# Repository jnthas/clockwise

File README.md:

**[Latest version 1.4.4 released!](https://github.com/jnthas/clockwise/releases/tag/v1.4.4)** | [See full change log](https://github.com/jnthas/clockwise/blob/main/CHANGELOG.md#144---2026-10-05)

---

**Clockwise** is an open-source smart wall clock that you can easily build yourself.  
It only needs:

- 64x64 RGB LED Matrix (HUB75 or HUB75E)
- ESP32 dev board
- 5V 3A power supply
- Jumpers

To simplify assembly, you can also use the [**WiseShield-32 DIY PCB kit**](https://www.elecrow.com/clockwise-diy-kit.html) — created in partnership with Elecrow especially for Clockwise.

---

## Features

- Real-time clock with customizable themes ("Clockfaces")
- Web-based interface for configuration
- [MCP tools and a desktop-client bridge](docs/MCP.md) for local AI-assisted control
- Open-source hardware and firmware
- Compatible with various PCBs or just simple wiring
- Community-driven

---

## Quick Start

### 1. Required Hardware

If you want to build it from scratch, you will need at least these components below. Follow the instructions on [Wiki]() to assemble it. 
- 64x64 RGB LED matrix (HUB75 or HUB75E)
- ESP32 Dev Board
- 5V 3A power supply
- Jumpers

Alternatively, we created a custom PCB that simplifies this process a lot. The kit includes not only the PCB but all components including sensors to make your clock smarter. Check the [WiseShield-32 PCB kit](https://www.elecrow.com/clockwise-diy-kit.html) out now!

### 2. Flash Firmware

- Go to: [https://clockwise.page](https://clockwise.page)
- Follow the on-screen steps to flash Clockwise and configure WiFi

For detailed instructions:  
👉 [See Wiki: Getting Started](https://github.com/jnthas/clockwise/wiki/%F0%9F%9A%80-Getting-Started)

---

## Clockfaces Gallery

You can choose from many creative Clockfaces — or make your own:

Mario Bros | Words | World Map | Castlevania | Pacman | Pokedex | Canvas
:--:|:--:|:--:|:--:|:--:|:--:|:--:
 |  |  |  |  |  | 

> Canvas is a special type of Clockface that is capable of rendering different themes described in a JSON file. More about **Canvas Clockface**: [Wiki page](https://github.com/jnthas/clockwise/wiki/Canvas-Clockface)

---

## How to Build

You can start developing and customizing Clockwise in two different ways:

1. **PlatformIO** — advanced usage for developers  
2. **ESP-IDF** — for full control  

👉 [Both are described in the Flashing section of the Wiki](https://github.com/jnthas/clockwise/wiki/%F0%9F%92%BE-Flashing-the-Firmware)

---

## Advanced Configuration

Clockwise offers a flexible set of options that you can adjust through its built-in Settings page:

* **WiFi settings** — easily update your network details without reflashing
* **Timezone & NTP server** — sync the clock accurately with automated NVS POSIX caching
* **Display brightness** — manual or smoothed automatic control (with optional LDR sensor)
* **Display rotation** — adjust orientation (0°, 90°, 180°, 270°) to match your setup
* **Clockface selection** — switch between installed Clockfaces or use Canvas themes
* **RGB order correction** — swap Blue/Green or Blue/Red pins to fix color mismatches
* **Hardware settings** — configure matrix shift driver (FM6124, etc.), I2S clock speed, and E-line pin
* **POSIX timezone string** — fine-tune timezone behavior or use offline overrides

👉 See the full guide here: [Advanced Configuration Wiki](https://github.com/jnthas/clockwise/wiki/%E2%9A%99%EF%B8%8F-Configuring-Clockwise)

---

## Community & Contributions

- Join the [Clock Club](https://github.com/jnthas/clock-club) to create your own Clockfaces
- Contributions and pull requests are welcome!  
👉 [Contributing Guide](https://github.com/jnthas/clockwise/wiki/%F0%9F%A4%9D-Contributing)

---

## License

Clockwise is released under the MIT License.

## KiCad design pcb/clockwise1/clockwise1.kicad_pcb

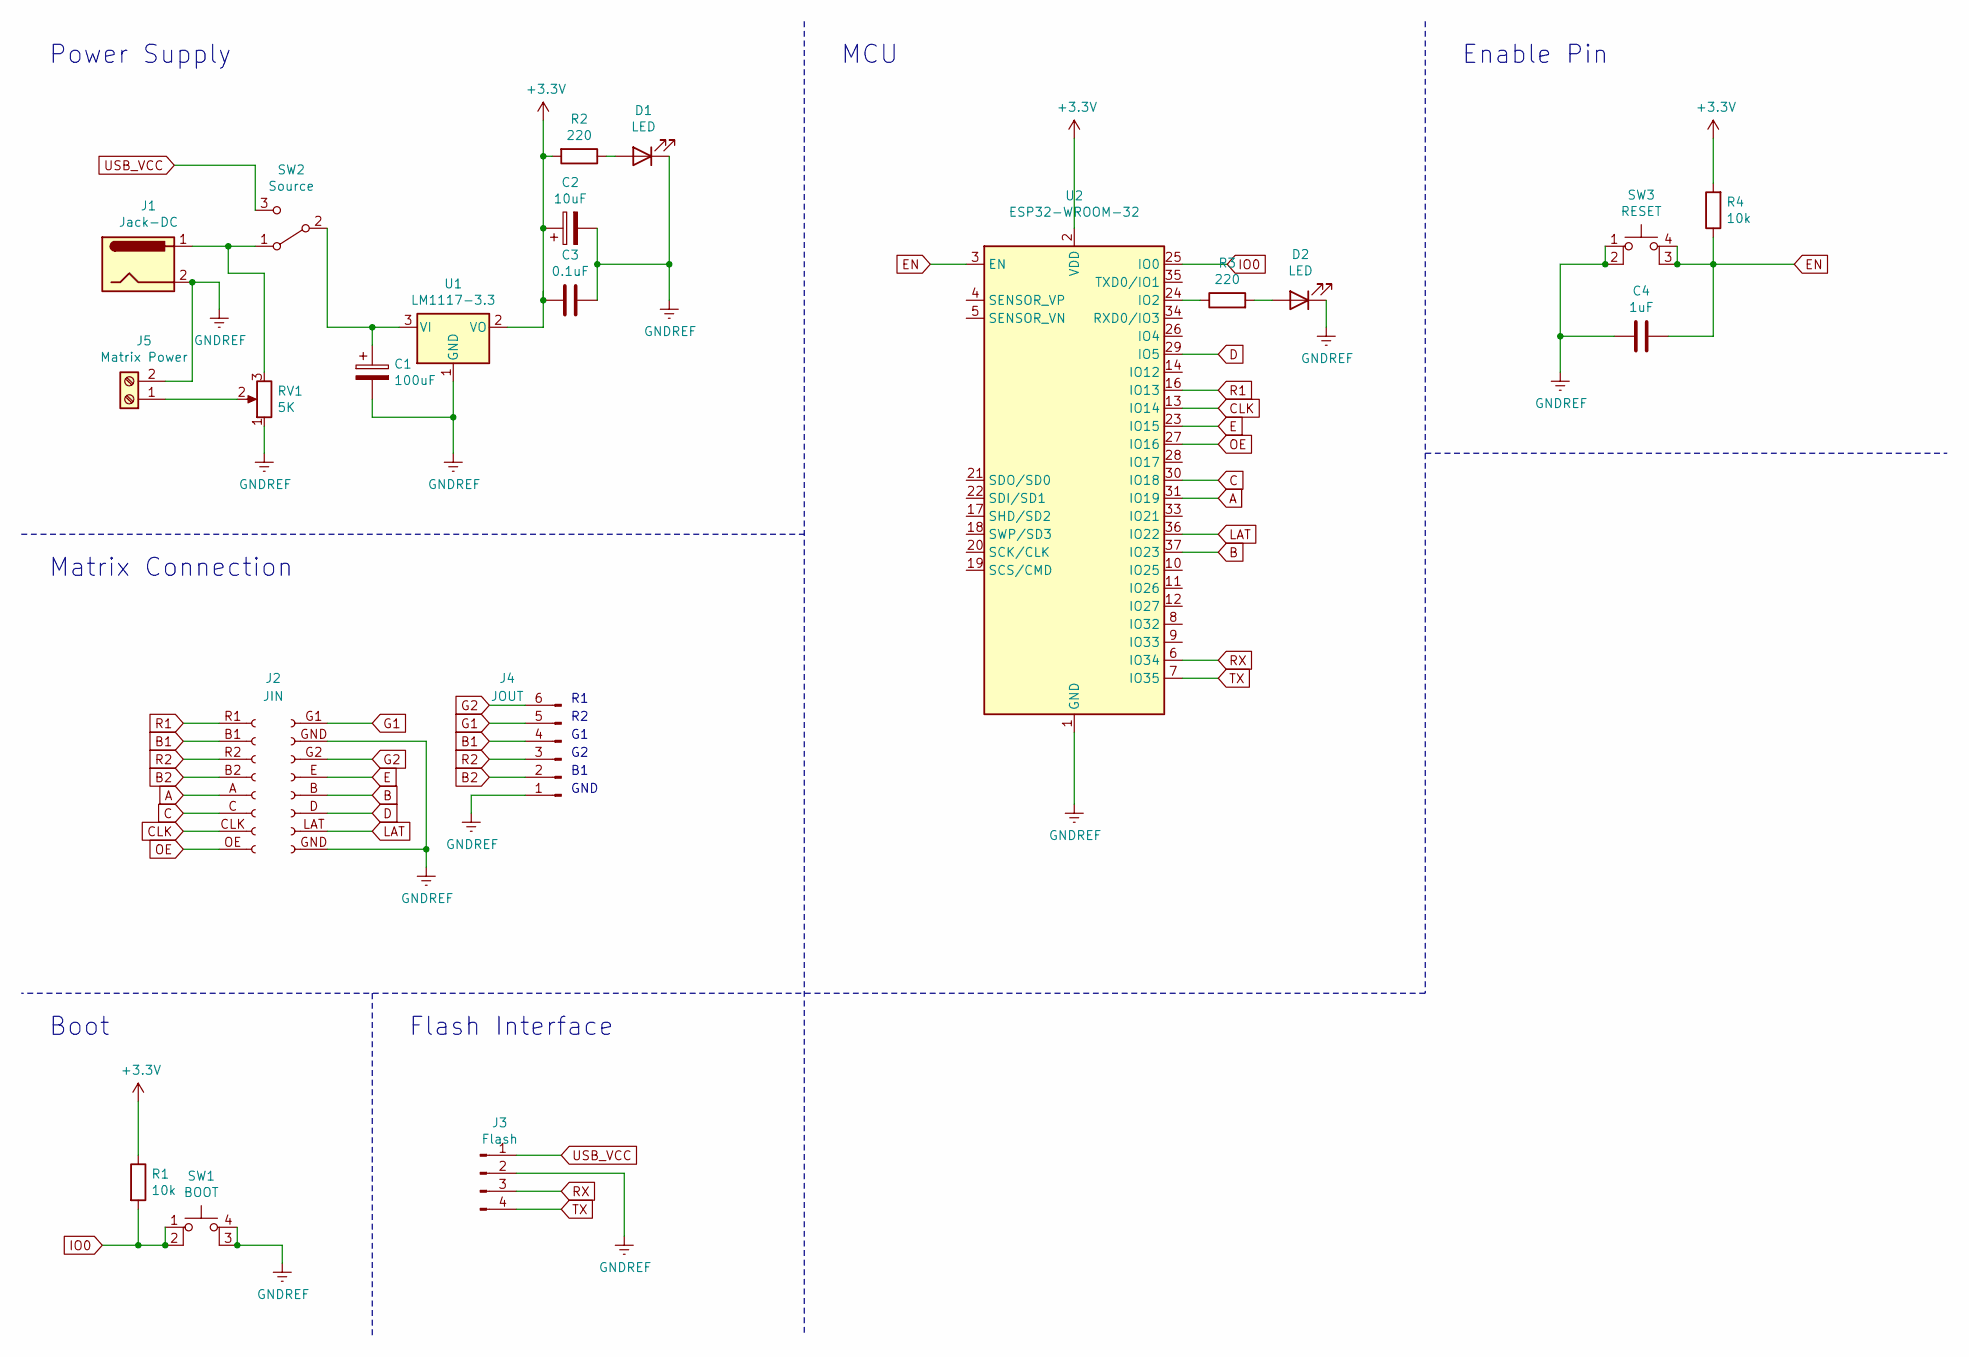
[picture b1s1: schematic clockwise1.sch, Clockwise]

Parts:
C1: 100uF; CP_Radial_D10.0mm_P5.00mm
C2: 10uF; CP_Radial_D10.0mm_P3.50mm
C3: 0.1uF; C_Disc_D5.0mm_W2.5mm_P5.00mm
C4: 1uF; CP_Radial_D10.0mm_P3.50mm
D1, D2: LED; LED_D3.0mm
J1: Jack-DC; BarrelJack_Horizontal
J2: JIN; PinSocket_2x08_P2.54mm_Vertical_SMD_LedMatrix
J3: Flash; PinHeader_1x04_P2.54mm_Vertical
J4: JOUT; PinHeader_1x06_P2.54mm_Vertical
J5: Matrix Power; TerminalBlock_Phoenix_MKDS-1,5-2-5.08_1x02_P5.08mm_Horizont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
R1, R4: 10k; R_Axial_DIN0207_L6.3mm_D2.5mm_P10.16mm_Horizontal
R2: 220; R_Axial_DIN0207_L6.3mm_D2.5mm_P10.16mm_Horizontal
R3: 220; R_Axial_DIN0207_L6.3mm_D2.5mm_P15.24mm_Horizontal
RV1: 5K; Potentiometer_Bourns_3386F_Vertical
SW1: BOOT; SW_PUSH
SW2: Source; SW_Slide_1P2T_CK_OS102011MS2Q
SW3: RESET; SW_PUSH
U1: LM1117-3.3; SOT-223
U2: ESP32-WROOM-32

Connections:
+3V3: C2.1, C3.2, R1.1, R2.2, R4.2, U1.2 (VO), U2.2 (VDD)
A: J2.A (Pin_5), U2.31 (IO19)
B: J2.B (Pin_12), U2.37 (IO23)
B1: J2.B1 (Pin_2), J4.4
B2: J2.B2 (Pin_4), J4.2
C: J2.C (Pin_6), U2.30 (IO18)
CLK: J2.CLK (Pin_7), U2.13 (IO14)
D: J2.D (Pin_11), U2.29 (IO5)
E: J2.E (Pin_13), U2.23 (IO15)
EN: C4.1, R4.1, SW3.3 (K), SW3.4 (A), U2.3 (EN)
G1: J2.G1 (Pin_16), J4.5
G2: J2.G2 (Pin_14), J4.6
GNDREF: C1.2, C2.2, C3.1, C4.2, D1.1 (K), D2.1 (K), J1.2, J2.GND (Pin_15), J3.2, J4.1, J5.2, RV1.1, SW1.3 (K), SW1.4 (A), SW3.1, SW3.2, U1.1 (GND), U2.1 (GND), U2.15 (GND), U2.38 (GND), U2.39 (GND)
IO0: R1.2, SW1.1, SW1.2, U2.25 (IO0)
LAT: J2.LAT (Pin_10), U2.36 (IO22)
unnamed: C1.1, SW2.2 (B), U1.3 (VI)
unnamed: D1.2 (A), R2.1
unnamed: D2.2 (A), R3.2
unnamed: J1.1, RV1.3, SW2.1 (A)
unnamed: J5.1, RV1.2
unnamed: R3.1, U2.24 (IO2)
OE: J2.OE (Pin_8), U2.27 (IO16)
R1: J2.R1 (Pin_1), U2.16 (IO13)
R2: J2.R2 (Pin_3), J4.3
RX: J3.3, U2.6 (IO34)
TX: J3.4, U2.7 (IO35)
USB_VCC: J3.1, SW2.3 (C)

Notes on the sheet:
Enable Pin
Power Supply
Boot
Flash Interface
Matrix Connection
MCU
GND

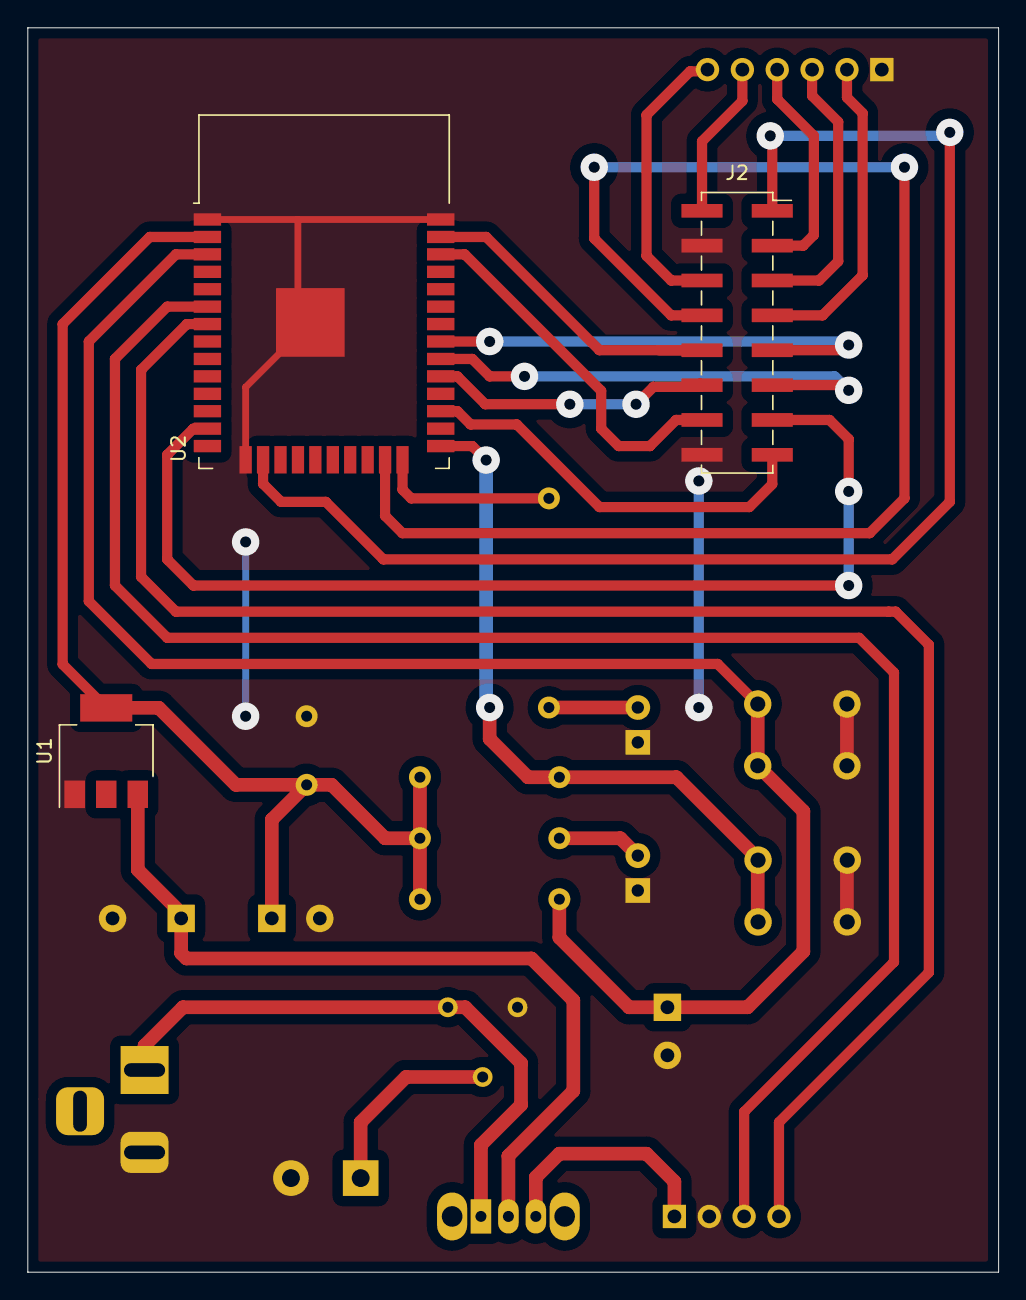
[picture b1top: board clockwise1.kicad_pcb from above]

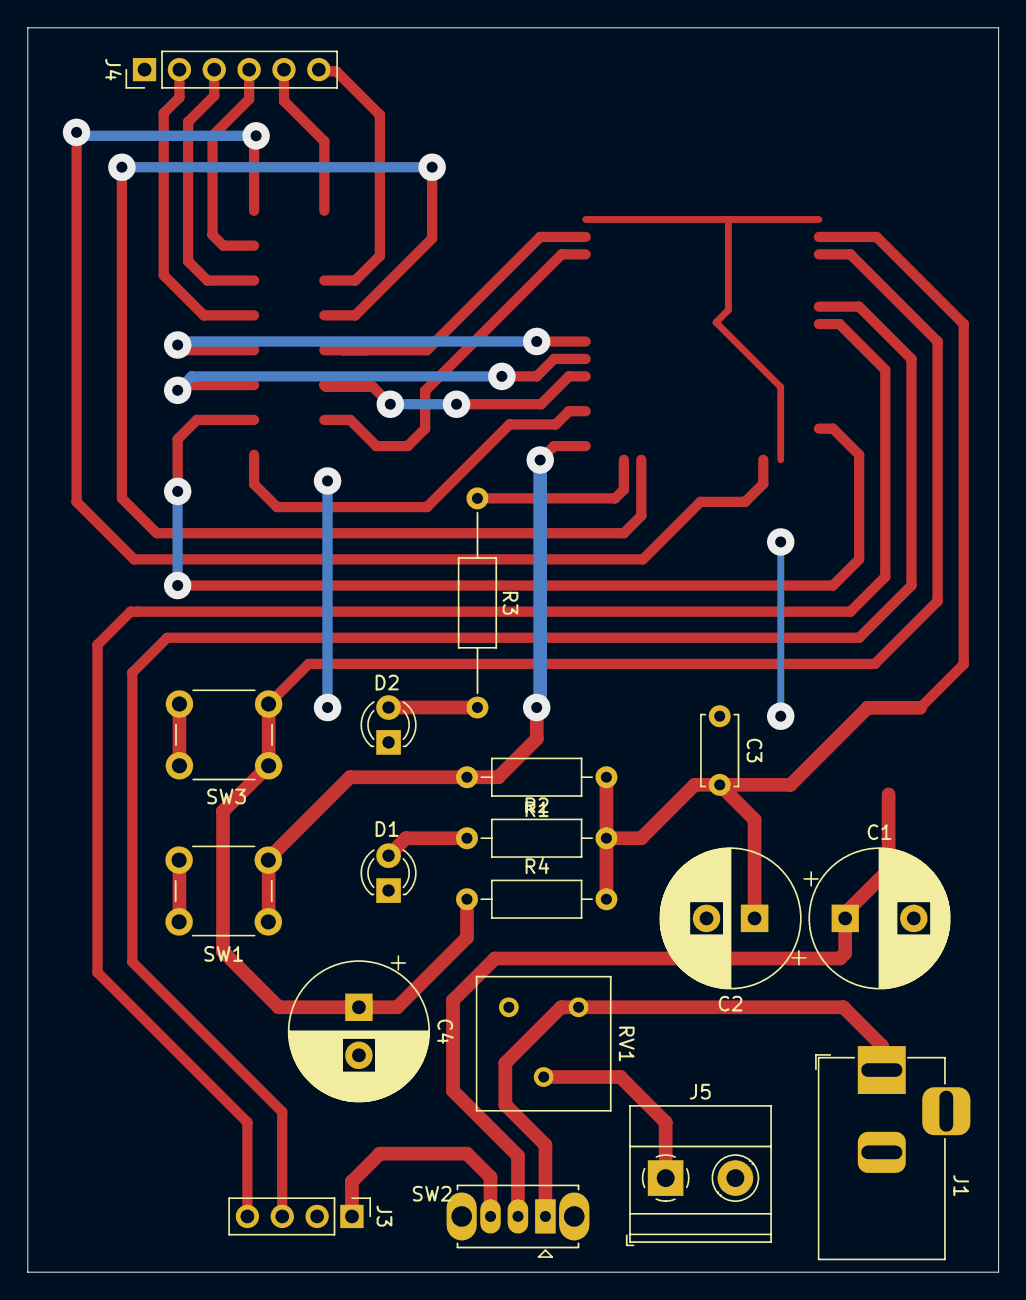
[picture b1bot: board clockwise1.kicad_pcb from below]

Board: 2 copper layers, 70.7 x 90.7 mm, 21 parts (18 on the bottom side), 27 nets.

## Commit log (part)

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2022-07-09 update clockfaces
2022-07-18 ci pipeline
2022-07-18 clockwise ci
2022-07-22 new version published
2022-07-22 new version published - cw-cf-0x03
2022-07-22 new version published - cw-cf-0x02
2022-07-22 new version published - cw-cf-0x04
2022-07-22 new version published - cw-cf-0x01
2022-07-22 reafactoring folder structure
2022-07-22 remove symlink
2022-08-07 add pacman clockface
2022-08-07 Add pacman build
2022-08-07 new version published - cw-cf-0x05
2022-08-07 new commits
2022-08-07 update cw-cf-05
2022-08-07 update submodules
2022-08-09 Add configuring wifi instructions
2022-09-26 Fix warning in WiFiConnect.H
    When compiling the code with '-Werror=format' the code fails to compile with this error:
    ```
    WiFiConnect.h: In member function 'void WiFiConnect::connect()':
    WiFiConnect.h:46:30: error: format '%s' expects argument of type 'char*', but argument 3 has type 'String' [-Werror=format=]
    ```
    This PR changes the code to satisfy the expected argument type.
2022-09-26 Add initial esp-idf support for clockwise.
    * Add project configuration menu for selecting the desired clockface
    * Add support for swapping Blue and Green colors, which is a common problem with some 64x64 HUB75 displays.
2022-09-26 Update submodule versions to include latest clockfaces.
    This is required because the Pull Requests containing the CMakeLists.txt files must be included in the version that is used.
    This update was created with `git submodule update --recursive --remote`
2022-10-03 Update pin E wiring
2022-10-06 Update WiFiManager to latest version, remove hack in CMakeLists.txt
    Now that tzapu/WiFiManager#1489 has been merged in, we can update the git submodule and remove the hack from CMakeLists.txt.
2023-03-09 Mention wifi AP + password
2023-03-24 Using improv-wifi
2023-04-01 Improv and settings page
2023-04-02 settings feature
2023-04-02 fix clockwise update bug
2023-04-02 Add News update
2023-04-16 add cw-cf-0x06
2023-04-16 new version published - cw-cf-0x06
2023-04-16 redesign fieldset
2023-04-30 add pins
2023-05-05 Update WiFiController.h
    return AP connection functionality
2023-05-05 fix wifi ap
2023-05-06 Improvements on setup wifi
2023-05-07 Add wifimanager submodule
2023-05-07 Add git module
2023-05-14 automatic bright control
2023-05-14 inc version
2023-05-14 add sponsoring url
2023-05-14 Improv must be used first before WifiMan
2023-05-17 firmware name by envvar
2023-05-31 First attempt at adding ntpServer config
2023-05-31 add ignore for VSCode config
2023-05-31 Update gitignore
2023-06-03 Minor fixes of NTP Server config
2023-06-04 [ABC] Add possibility to turnoff display
2023-06-09 Add firmware ver on settings page
2023-06-10 Add LDR Pin param
2023-06-10 Read pin method
2023-06-11 (esp-idf) Add build definitions for `CW_FW_VERSION` and `CW_FW_NAME`.
    The project fails to compile on ESP-IDF because these definitions are missing.
    I'm trying to fix https://github.com/jnthas/clockwise/issues/16 and this error is preventing the project from compiling.
2023-06-11 esp-idf compatibility
2023-06-11 (ESP-IDF) Add missing `REQUIRES`. Update `Improv-WiFi-Library` submodule to latest version.
    * Change `REQUIRES` to `PRIV_REQUIRES` for faster compile times (https://cmake.org/pipermail/cmake/2016-May/063400.html)
    * Add `Adafruit-GFX-Library` as a direct requirement because it's used in `lib/cw-gfx-engine/Locator.h`
    * Add `Improv-WiFi-Library` as a direct requirement because it's used in `firmware/src/main.cpp` and `firmware/lib/cw-commons/WiFiController.h`
    This is to help fix https://github.com/jnthas/clockwise/issues/16.
2023-06-11 remove link to clockface
2023-06-11 Change `REQUIRES` -> `PRIV_REQUIRES`. Add dependency on `Adafruit-GFX-Library`
    * Change `REQUIRES` to `PRIV_REQUIRES` for faster compile times (https://cmake.org/pipermail/cmake/2016-May/063400.html)
    * Add `Adafruit-GFX-Library` as a direct requirement because it's used in `lib/cw-gfx-engine/Locator.h`
2023-06-11 Add `esp-idf` CI workflow
    This should help prevent breakages of `esp-idf` users.
2023-07-01 Canvas feature
2023-07-01 update repo
2023-07-01 new clockface
2023-07-01 add Canvas new section
2023-07-01 new version 1.4
2023-07-01 update esp-idf
2023-07-01 new version published - cw-cf-0x07
2023-07-01 Update version
2023-07-16 Create CNAME
2023-07-19 Added manual Posix timezone string option.
2023-07-20 Compiled list of Posix timezone strings using the ezTime server script
2023-07-21 Reworded settings card
2023-07-21 Updated link to Posix strings
    Linked to https://github.com/nayarsystems/posix_tz_db/blob/master/zones.csv
2023-07-22 Add manual posix param
2023-08-27 Set google NTP as default
2023-08-27 update clockface 0x07
2023-09-11 add API documentation Use a saparate page for describing the API to readers on github pages and an OpenAPI specification file for devs who would like to use their own tools
2023-09-12 add gitignore file and exclude the generated site
2023-09-21 added descriptions to x-header fields
2023-10-15 remove ssl wifi
2023-11-05 Create LICENSE
2023-12-20 Added option to rotate display to web interface.
2024-02-20 Add ntp sync in main loop
    Add ezt::events() in main loop for ntp sync (every 30 minutes by default. This should fix any out of sync issues people might have ( I had them :))
2024-04-21 canvas updated
2024-04-21 version 1.4.2
2024-04-25 optimization auto bright control and set ntp failed timeout to 10s
2024-04-26 add currentValue > ldrMax? logic to ensure that result slot is between 1 and 10
2024-05-11 fix esp-idf errors
2025-02-05 Adding support for chained 64x32 panels
2025-02-05 Remove trailing whitespace
2025-02-05 Avoid definining unnecessary constants
2025-06-19 create the welcome page
2025-06-19 add link to wiki
2025-06-20 change text
2025-06-20 update welcome page
2025-06-20 add pcb photos
2025-06-22 add troubleshooting guide
2025-10-03 Fix for not starting AP if SSID empty (e.g. flashing from platformio to new esp32)
2025-10-03 Add configuration to swap blue and red. Fix for #96
2025-10-04 Add Web configuration for HW parameter: driver, i2c speed, E pin
2025-11-10 adds BLE server class
2026-01-28 Update for MarioExtended
2026-02-17 Fix matrix panel lib version
2026-06-05 Remove support of ESP-IDF
